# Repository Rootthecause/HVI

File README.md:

Dear Formula Student Teams,

I've designed a High Voltage Indicator in accordance with [EV 5.4.8 (Rules 2026_v1.0)](https://www.formulastudent.de/fileadmin/user_upload/all/2026/rules/FS-Rules_2026_v1.0.pdf#subsubsection.4.5.4.8) to replace our heavy and bulky voltmeter. This device can supply between 5 V and 24 V (depending on the configuration) at a maximum of 1 W (isolated) or 3 W (non-isolated) from a 40 V to 800 V source. Two LEDs on the back indicate the presence of high voltage, so it can be mounted either directly to a viewing window in the TSAC or elsewhere with a cable to an external LED. As it is basically an HV step-down converter, it can also be used for any other application, e.g. to start a DC/DC (for LVS supply) from HV with the added benifit of significantly higher efficiency (50-80%) compared to an LDO (few percent).<br>

Most components used are standard parts, but key components include URLs linking to Mouser or datasheets (for quick access: highlight part, press "D").<br>

This design is published as open-source hardware under the CERN-OHL-W license and can be found on GitHub: https://github.com/Rootthecause/HVI<br>
If you have received any files from me directly, please do not share or publish them, as I don't want others to share files which may be incomplete or contain errors.<br>

Although this design has passed FSG scrutineering and has been operating without any issues for over 2 Years, always manufacture at your own risk!<br>

If you encounter any bugs or have suggestions for improvement, please feel free to use the GitHub [issues form](https://github.com/Rootthecause/HVI/issues/new). For discussions and technical questions, kindly use the [discussion bord](https://github.com/Rootthecause/HVI/discussions).<br>

Have fun. Do not lick things with spark symbols on :) 

Best regards,
Rootthecause

**Backside**

**Front with case (SLA printed)**

# VERSION HISTORY
```
v0	DIY etched prototype. Working, but not optimized
v1.0	commercial PCB with optimized components, tested for more than 3 months.
v1.1	Small layout changes and improvements, not tested but should be fine
```

# Q&A
Q: 	&ensp;How is the Rule [EV 5.4.8 (Rules 2026_v1.0)](https://www.formulastudent.de/fileadmin/user_upload/all/2026/rules/FS-Rules_2026_v1.0.pdf#subsubsection.4.5.4.8) "must continuously **illuminate at its
full brightness** whenever a voltage greater than 60 V DC" fullfilled?<br>
A: 	&ensp;The HVI is a self-ocillating high voltage stepdown with voltage regulation. <br>
The output will stay constant at around 5 V regardless of the input voltage, thus the LEDs are always lit at full brightness.
<br>

Q: 	&ensp;How is the Rule [EV 5.4.8 (Rules 2026_v1.0)](https://www.formulastudent.de/fileadmin/user_upload/all/2026/rules/FS-Rules_2026_v1.0.pdf#subsubsection.4.5.4.8) "greater than 60 V DC" fullfilled?"<br>
A: 	&ensp;The Rule does not require a logic to light up the LEDs exacly at 60 V - but it must be lit by then. So if the LEDs light up below 60V, it sufficiently met the rule. 
Once the HVI has turned on at around 39 V it will stay on until the voltage falls below around 12 V.<br>

Q: 	&ensp;My team is using the HVI v1.1 design. Are there any changes regarding the Rules 2026 required?<br>
A: 	&ensp;No. At the moment there is no rule known requireing a change. The rule change in [EV 5.4.8 (Rules 2026_v1.0)](https://www.formulastudent.de/fileadmin/user_upload/all/2026/rules/FS-Rules_2026_v1.0.pdf#subsubsection.4.5.4.8) was meet already by the HVI v1.1 design.<br>

Q: 	&ensp;Why are 2x 4.7 mH inductors used instead of a 10 mH inductor?<br>
A: 	&ensp;You will rarely find maximum voltage values for SMD inductors, so just an extra precaution.<br>

Q: 	&ensp;Why is there no output fuse?<br>
A: 	&ensp;The VIPER06 can be short-circuited indefinitely.<br>

Q: 	&ensp;I need [insert voltage here], can I do that?<br>
A: 	&ensp;You can either change PS1 (12 V to 3.3 V to 24 V converters available) 
	or (when used directly without PS1) the feedback voltage divider can be altered.
	I do not reccomend going above 23.5 V because the IC's VDD voltage will be clamped, 
	which could lead to high losses or destruction of the IC. Going below 11.5 V 
	will use the internal high-voltage generator as IC's VDD supply (higher losses).
	So ideally, stay between 12 V and 23 V.<br>

Q: 	&ensp;Where do I get a cheap high voltage source for testing?<br>
A: 	&ensp;I have been using one for 10€ from amazon for many years, which can generate up to 
	800 V (when both -+400 V rails are used) from a 8 to 32 V source (15 V input delivers most HV power, 25 W max.).
	If you want to support me, you can use my affiliate link where I get a small commission 
	when a purchase is made: https://amzn.to/3TRJJif<br>
	In the docs there is an additional folder 'HV Source' for a 3D-printed case which also 
	uses a rotary potentiometer instead of the trim pot. If there is enough interest, I will make a build guide for it.<br> 
	Please add 100 uF (check voltage rating!) or more externally to the output, otherwise the feedback loop can be unstable.<br> 
	
Q: 	&ensp;I need more Power!<br>
A: 	&ensp;A smaller Inductor value could help, but be aware that the minimum on-time is 400 ns.
	At high input voltages this could lead to overcurrent when using small inductor values.<br>

Q: 	&ensp;Why is the text "Voltage Indicator", "Designed by XXX" and "HVI vX.X" not editable?<br>
A:	&ensp;I like to use a font (Futured) for visuals which is not pre-installed on most systems. 
	Importing it as a logo is easier to retain it.<br> 

Q: 	&ensp;Some 3D models on the PCB are missing.<br>
A:	&ensp;They are not included due to licence terms. However, you can download them from https://www.samacsys.com/ using the Mouser link provided in the properties of the KiCAD components.<br> 

Q:	&ensp;This is open source. Can I modify it? Can I sell it?<br>
A:	&ensp;Sure! But please use your own version numbering and change "Designed by Rootthecause" 
	to "Designed by [Your Name] based on a design by Rootthecause". 
	As this is licensed under CeRN OHL v2 Weakly Reciprocal, you must disclose the source, 
	state changes and use the same license if used for non private projects.
	Learn more about this here: https://choosealicense.com/licenses/cern-ohl-w-2.0/<br>

Q:	&ensp;I've got a question not listed here, can I contact you?<br>
A:	&ensp;Please use the [issues form](https://github.com/Rootthecause/HVI/issues/new) on GitHub for techical related questions.<br> 

Q:	&ensp;Is there a way to support your projects?<br>
A:	&ensp;I welcome any feedback on this project to make it better for everyone. Otherwise, if you would like to support me in working on this and other projects, you can also leave a donation. https://ko-fi.com/rootthecause<br>

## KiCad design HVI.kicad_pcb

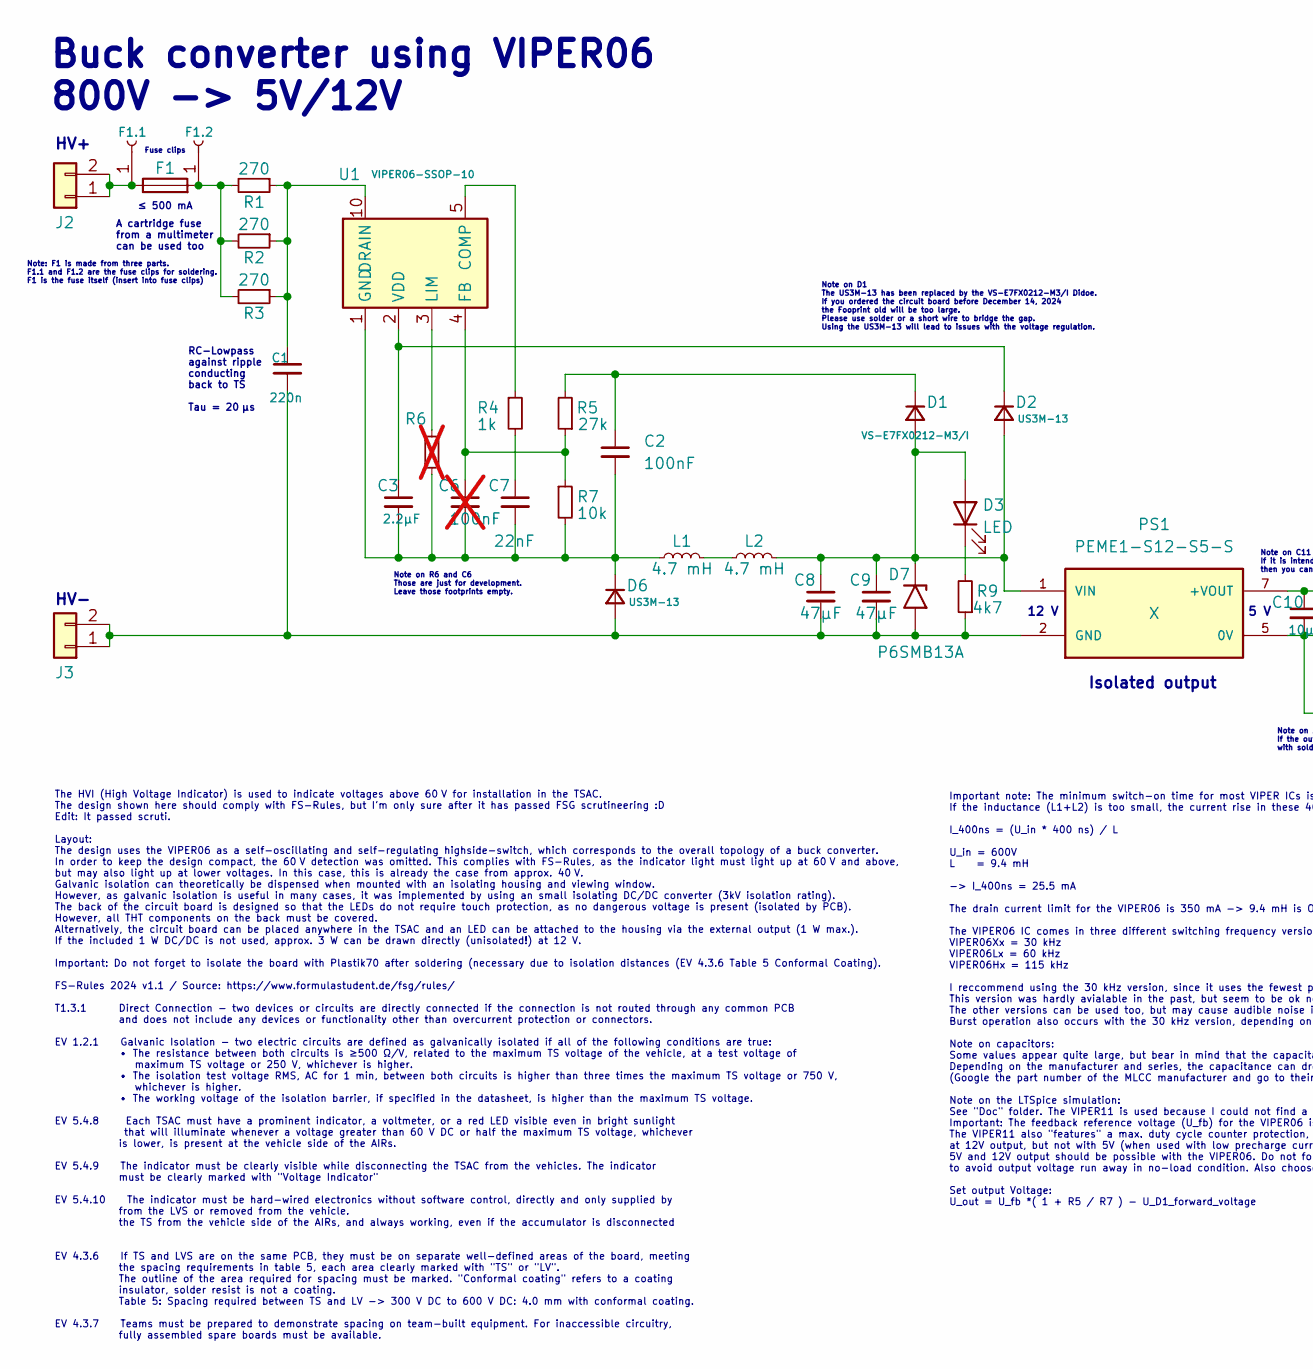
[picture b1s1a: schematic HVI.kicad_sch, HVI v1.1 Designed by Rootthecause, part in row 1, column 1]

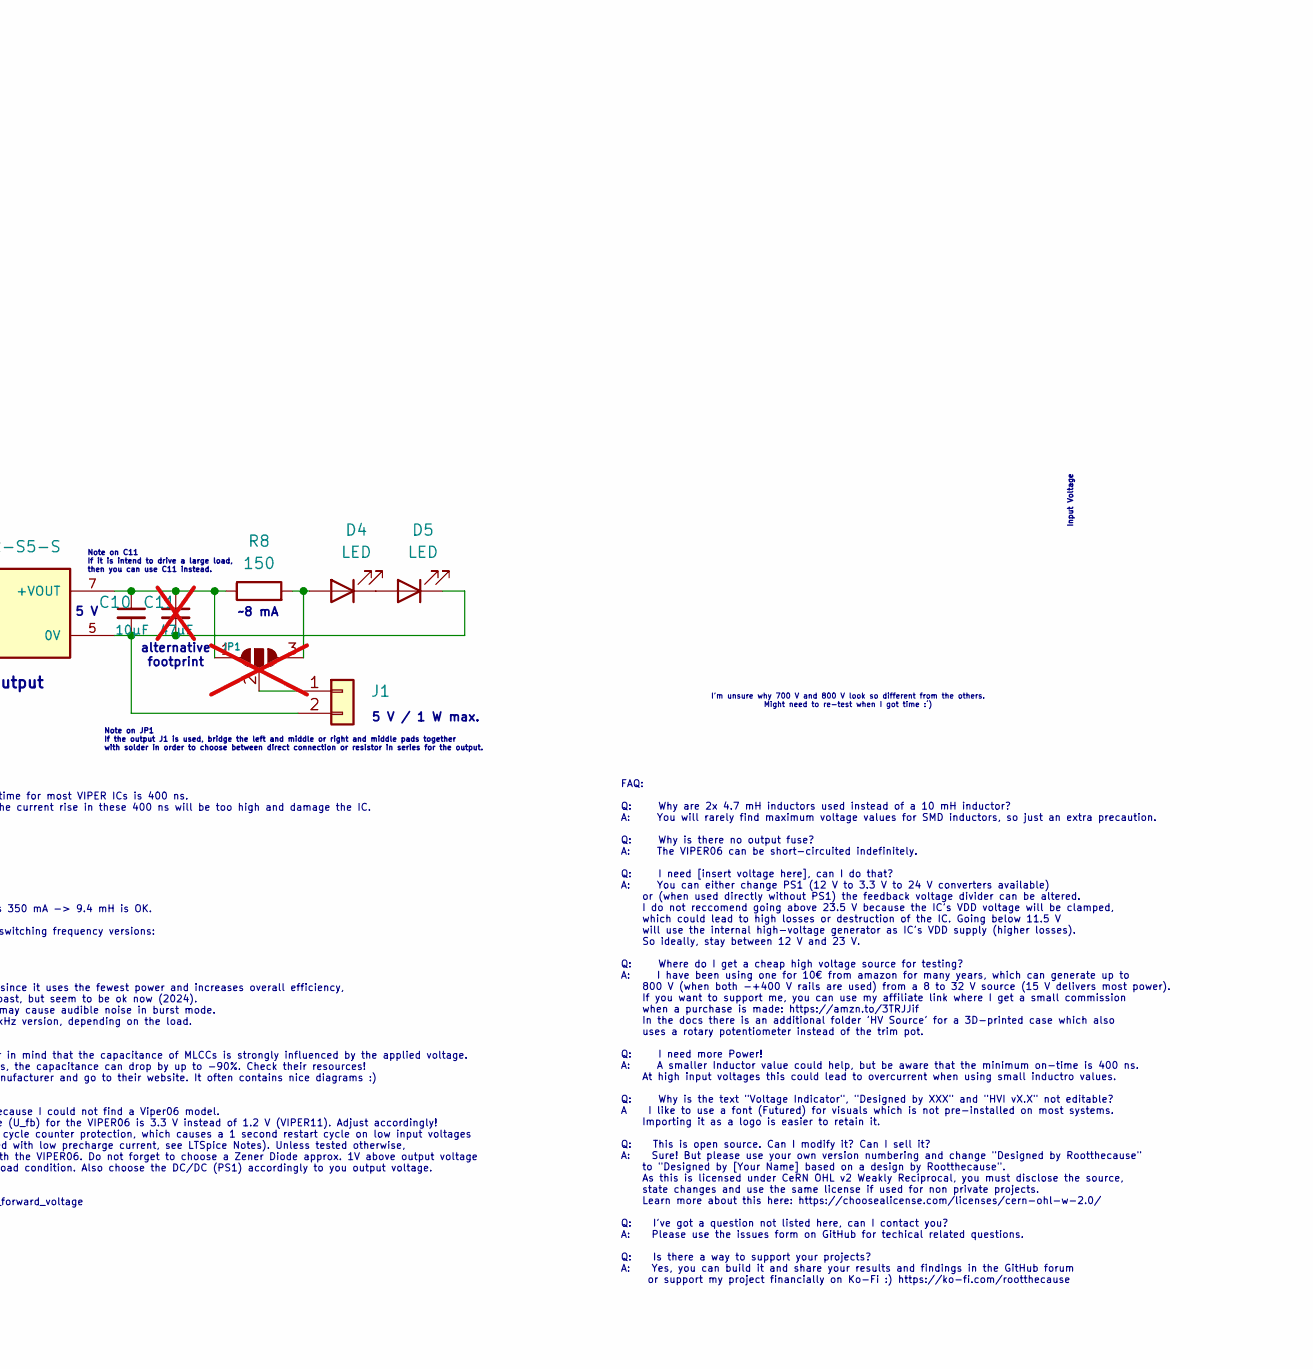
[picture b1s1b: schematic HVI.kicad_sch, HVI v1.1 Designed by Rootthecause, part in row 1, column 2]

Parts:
C1: 220n; C_2220_5650Metric; Mouser 810-C5750X7R2J224K
C2: 100nF; C_0603_1608Metric_Pad1.08x0.95mm_HandSolder; Mouser 81-GRM188R72A103MA1J
C3: 2.2µF; C_0603_1608Metric_Pad1.08x0.95mm_HandSolder; Mouser 963-UMK107BBJ225KA-T
C6: 100nF; C_0603_1608Metric_Pad1.08x0.95mm_HandSolder; not fitted
C7: 22nF; C_0603_1608Metric_Pad1.08x0.95mm_HandSolder; Mouser 80-C0603C223J3RAUTO
C8, C9: 47µF; C_1210_3225Metric_Pad1.33x2.70mm_HandSolder; Mouser 963-E32MAB5476MPNDTJ
C10: 10µF; C_0603_1608Metric_Pad1.08x0.95mm_HandSolder; Mouser 81-GRM188R6YA106MA3J
C11: 47µF; C_1210_3225Metric_Pad1.33x2.70mm_HandSolder; not fitted
D1: VS-E7FX0212-M3/I; D_SMF; Mouser 78-VS-E7FX0212-M3/I
D2, D6: US3M-13; D_SMC; Mouser 621-US3M-13
D3, D4, D5: LED; LED_0603_1608Metric_Pad1.05x0.95mm_HandSolder; Mouser 604-APTD1608LSURCK
D7: P6SMB13A; D_SMB; Mouser 652-P6SMB13A
F1: ≤ 500 mA, solder Fuse Clips F1.1 and F1.2 and ins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; Fuseholder0,25Zoll_32mm_littlefuse_102_122; Mouser 530-0ADAC0250-BE
F1.1, F1.2: Fuse Clips; -; Mouser 576-01220083Z
J1, J2, J3: Conn_01x02; Molex_Micro-Fit_3.0_43650-0215_1x02_P3.00mm_Vertical; Mouser 538-43650-0215
JP1: SolderJumper_3_Open; SolderJumper-3_P1.3mm_Open_RoundedPad1.0x1.5mm_NumberLabels; not fitted
L1, L2: 4.7 mH; L_Bourns_SRR1208_12.7x12.7mm; Mouser 652-SRR1208-472KL
PS1: PEME1-S12-S5-S; CONV_PEME1-S5-S5-S; PARTREV 1.02; Mouser 490-PEME1-S12-S5-S
R1, R2, R3: 270; R_1206_3216Metric_Pad1.30x1.75mm_HandSolder; Mouser 755-KTR18EZPF2700
R4: 1k; R_0603_1608Metric_Pad0.98x0.95mm_HandSolder; Mouser 71-CRCW06031K00FKEE
R5: 27k; R_0603_1608Metric_Pad0.98x0.95mm_HandSolder; Mouser 603-AC0603FR-0727KL
R6: -; R_0603_1608Metric_Pad0.98x0.95mm_HandSolder; not fitted
R7: 10k; R_0603_1608Metric_Pad0.98x0.95mm_HandSolder; Mouser 603-AC0603JR-0710KL
R8: 150; R_0603_1608Metric_Pad0.98x0.95mm_HandSolder; Mouser 603-AC0603FR-10150RL
R9: 4k7; R_0603_1608Metric_Pad0.98x0.95mm_HandSolder; Mouser 603-RC0201FR-074K7L
U1: VIPER06-SSOP-10; SSOP-10_3.9x4.9mm_P1.00mm; Mouser 511-VIPER06XSTR

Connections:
unnamed: C1.1, R1.1, R2.1, R3.1, U1.6 (DRAIN), U1.7 (DRAIN), U1.8 (DRAIN), U1.9 (DRAIN), U1.10 (DRAIN)
unnamed: C7.1, R4.2
unnamed: C8.1, C9.1, D1.2 (A), D2.2 (A), D3.2 (A), D7.1 (A1), L2.2, PS1.1 (VIN)
unnamed: C2.1, D1.1 (K), R5.2
unnamed: C3.1, D2.1 (K), U1.2 (VDD)
unnamed: D3.1 (K), R9.2
unnamed: D4.2 (A), JP1.3 (B), R8.2
unnamed: D4.1 (K), D5.2 (A)
unnamed: C10.2, C11.2, D5.1 (K), J1.2, PS1.5 (0V)
unnamed: C1.2, C8.2, C9.2, D6.2 (A), D7.2 (A2), J3.1, J3.2, PS1.2 (GND), R9.1
unnamed: C2.2, C3.2, C6.2, C7.2, D6.1 (K), L1.1, R6.2, R7.2, U1.1 (GND)
unnamed: F1.2, F1.2.1, R1.2, R2.2, R3.2
unnamed: J1.1, JP1.2 (C)
unnamed: F1.1, F1.1.1, J2.1, J2.2
unnamed: C10.1, C11.1, JP1.1 (A), PS1.7 (+VOUT), R8.1
unnamed: L1.2, L2.1
unnamed: R4.1, U1.5 (COMP)
unnamed: C6.1, R5.1, R7.1, U1.4 (FB)
unnamed: R6.1, U1.3 (LIM)

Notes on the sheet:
Note on C11 If it is intend to drive a large load, then you can use C11 instead.
I'm unsure why 700 V and 800 V look so different from the others. Might need to re-test when I got time :‘)
Buck converter using VIPER06 800V -> 5V/12V
FAQ: Q: Why are 2x 4.7 mH inductors used instead of a 10 mH inductor? A: You will rarely find maximum voltage values for SMD inductors, so just an extra precaution. Q: Why is there no output fuse? A: The VIPER06 can be short-circuited indefinitely. Q: I need [insert voltage here], can I do that? A: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
HV-
5 V / 1 W max.
The HVI (High Voltage Indicator) is used to indicate voltages above 60 V for installation in the TSAC. The design shown here should comply with FS-Rules, but I'm only sure after it has passed FSG scrutineering :D Edit: It passed scruti. Layout: The design uses the VIPER06 as a self-oscillating and 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
Input Voltage
≤ 500 mA
Isolated output
5 V
Note on R6 and C6 Those are just for development. Leave those footprints empty.
RC-Lowpass against ripple conducting back to TS Tau = 20 µs
~8 mA
Note: F1 is made from three parts. F1.1 and F1.2 are the fuse clips for soldering. F1 is the fuse itself (insert into fuse clips)
12 V
alternative footprint
Note on JP1 If the output J1 is used, bridge the left and middle or right and middle pads together with solder in order to choose between direct connection or resistor in series for the output.
Fuse clips
A cartridge fuse from a multimeter can be used too
Important note: The minimum switch-on time for most VIPER ICs is 400 ns. If the inductance (L1+L2) is too small, the current rise in these 400 ns will be too high and damage the IC. I_400ns = (U_in * 400 ns) / L U_in = 600V L = 9.4 mH -> I_400ns = 25.5 mA The drain current limit for the VIPER06 is 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
HV+
Note on D1 The US3M-13 has been replaced by the VS-E7FX0212-M3/I Didoe. If you ordered the circuit board before December 14, 2024 the Fooprint old will be too large. Please use solder or a short wire to bridge the gap. Using the US3M-13 will lead to issues with the voltage regulation.

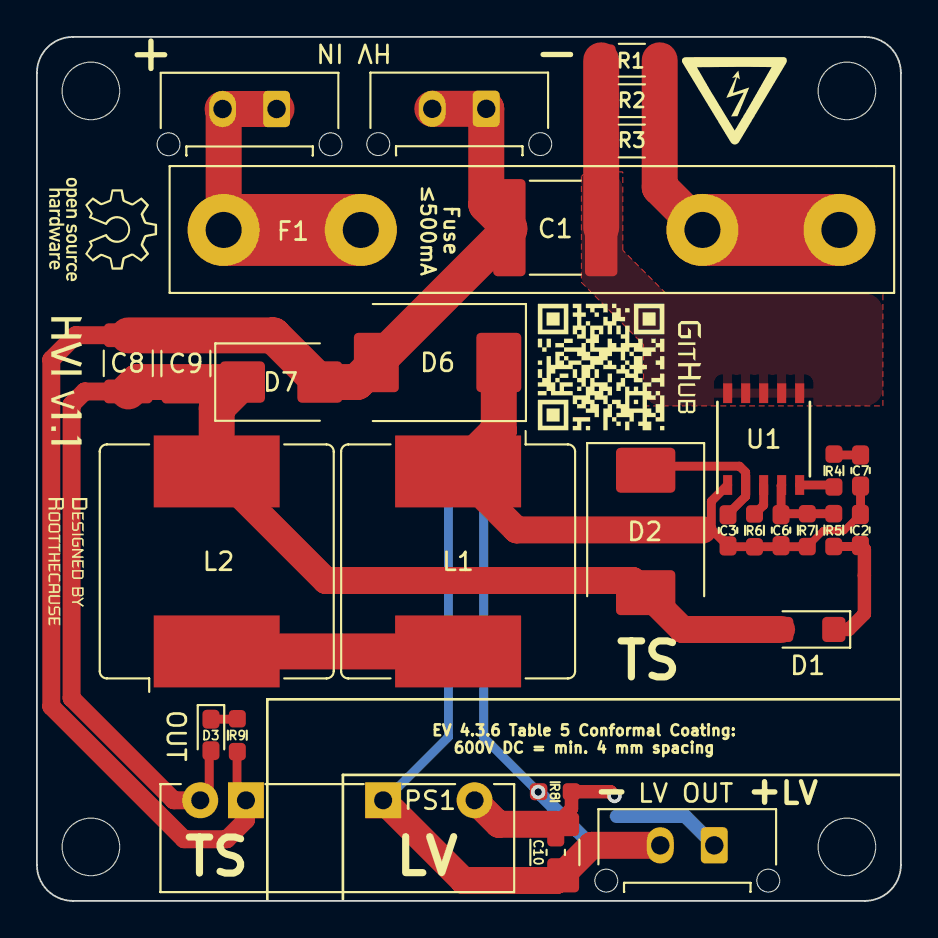
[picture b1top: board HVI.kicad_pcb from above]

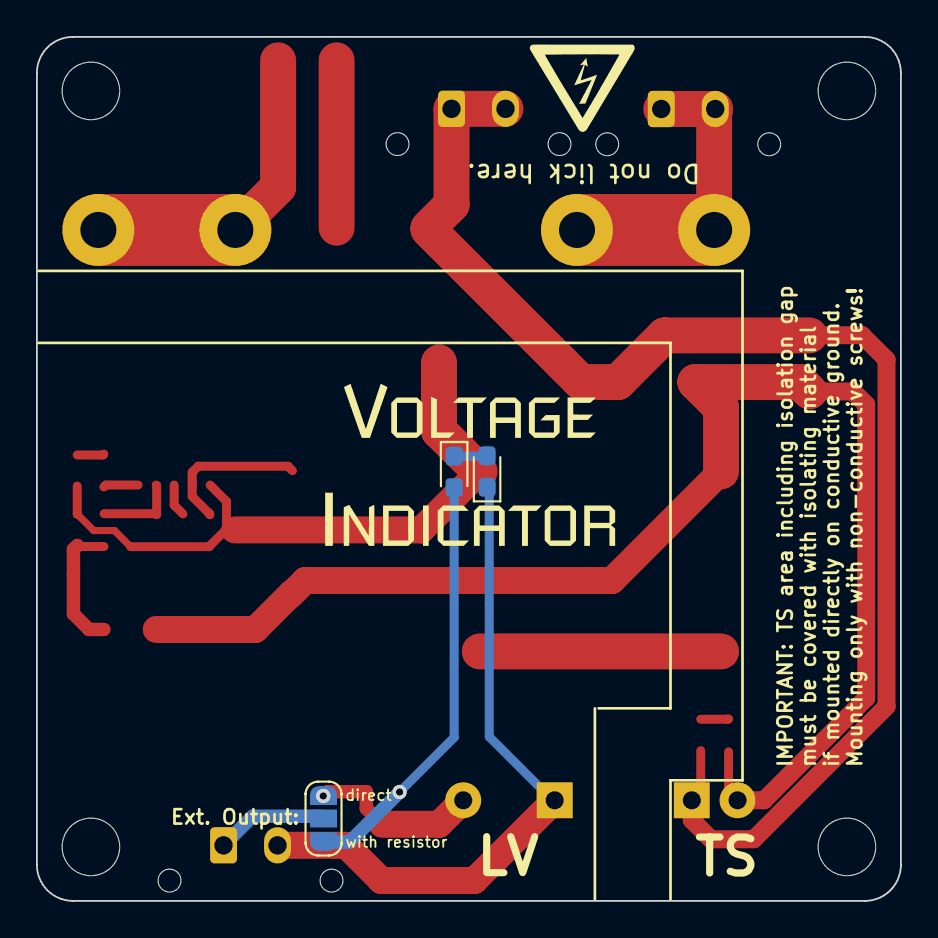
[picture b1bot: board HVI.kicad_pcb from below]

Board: 2 copper layers, 48.0 x 48.0 mm, 38 parts (3 on the bottom side), 19 nets.

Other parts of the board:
MK1, MK2, MK3, MK4: Mounting_Hole; MountingHole_3.2mm_M3_DIN965

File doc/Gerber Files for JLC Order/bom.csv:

Designator,Footprint,Quantity,Value,LCSC Part #
C1,2220,1,220n,
C10,0603,1,10µF,
C2,0603,1,100nF,
C3,0603,1,2.2µF,
C7,0603,1,22nF,
"C8, C9",1210,2,47µF,
D1,D_SMF,1,VS-E7FX0212-M3/I,
"D2, D6",D_SMC,2,US3M-13,
"D3, D4, D5",0603,3,LED,
D7,D_SMB,1,P6SMB13A,
F1,"Fuseholder0,25Zoll_32mm_littlefuse_102_122",1,"≤ 500 mA, solder Fuse Clips F1.1 and F1.2 and insert F1",
"J1, J2, J3",Molex_Micro-Fit_3.0_43650-0215_1x02_P3.00mm_Vertical,3,Conn_01x02,
JP1,SolderJumper-3_P1.3mm_Open_RoundedPad1.0x1.5mm_NumberLabels,1,SolderJumper_3_Open,
"L1, L2",L_Bourns_SRR1208_12.7x12.7mm,2,4.7 mH,
PS1,CONV_PEME1-S5-S5-S,1,PEME1-S12-S5-S,
"R1, R2, R3",1206,3,270,
R4,0603,1,1k,
R5,0603,1,27k,
R7,0603,1,10k,
R8,0603,1,150,
R9,0603,1,4k7,
U1,SSOP-10_3.9x4.9mm_P1.00mm,1,VIPER06-SSOP-10,

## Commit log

2024-10-08 updated readme hv source
2024-10-23 Update README.md
    fixed typo
2024-10-23 Update README.md
    added badges
2024-10-23 Update README.md
    removed unnecessary files structure
2024-12-14 Changed D1, updated BOM
2024-12-15 removed unclear component source
2024-12-19 changed C2, DNP for C6, added Fuse Clips F1.1 and F1.2
2025-03-09 fixed BOM error, added additional component URLs
2025-05-22 Added Mouser and LCSC Numbers. Updated to KiCad 9
2025-05-22 Updated KiCAD Tag in README.md
2026-05-05 Updated Gerber files see issue #7
